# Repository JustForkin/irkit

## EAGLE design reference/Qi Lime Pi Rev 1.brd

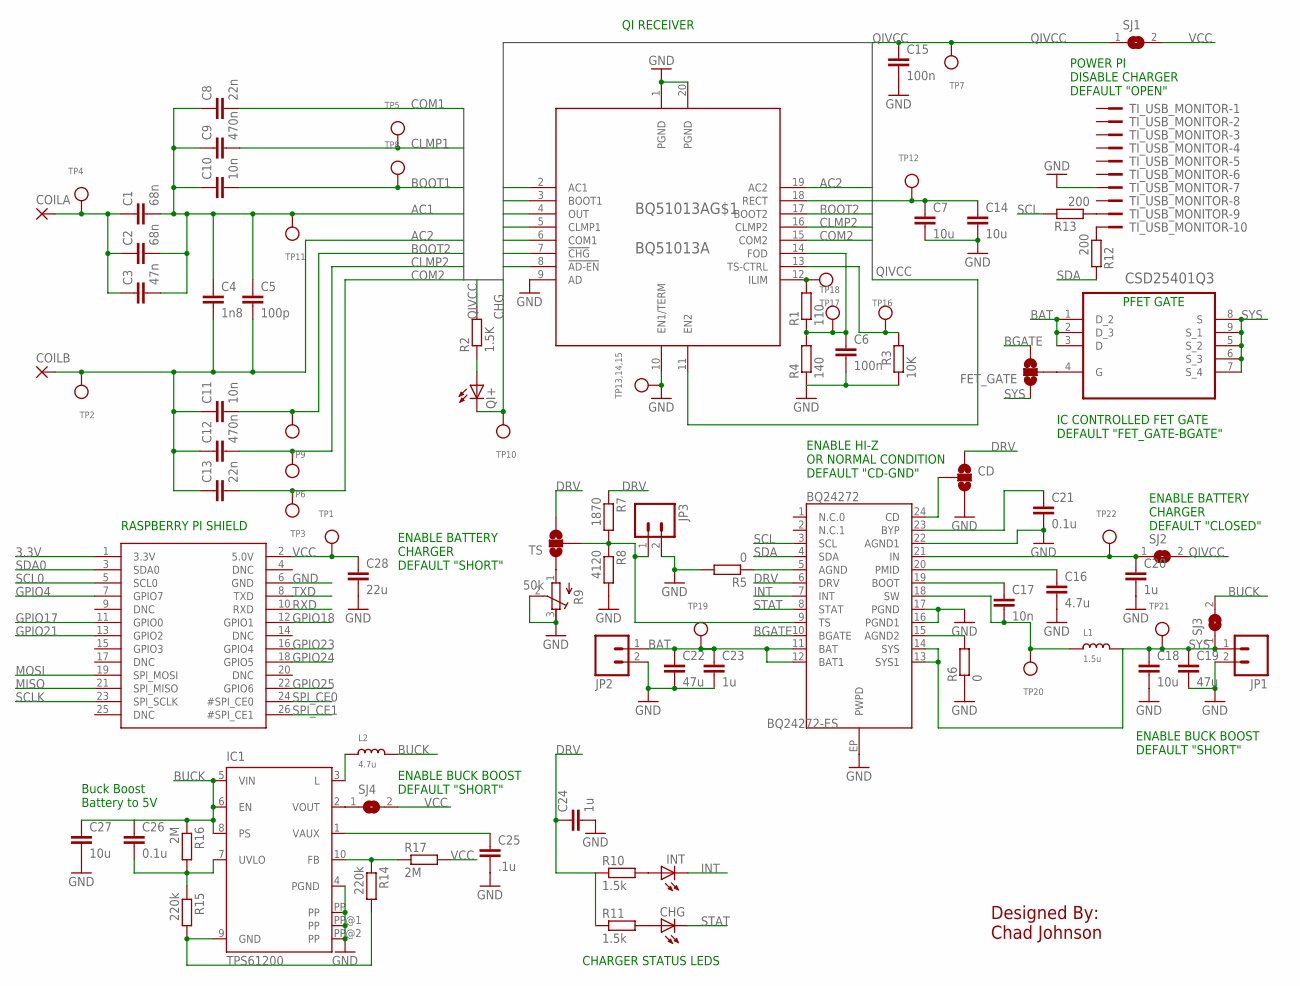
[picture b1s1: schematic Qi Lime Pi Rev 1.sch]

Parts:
BQ24272: BQ24272-ES; QFN-24_ALT2
BQ51013A: BQ51013A; RHL_R-VQFN-N20
C1, C2: 68n; C0603K; MPN C0603C682K5RACTU
C3: 47n; C0603K; MPN C0603C473K5RACTU
C4: 1n8; C0603K; MPN C0603C182K5RACTU
C5: 100p; C0603K; MPN C0603C101K5RACTU
C6, C15: 100n; C0603K
C7, C14, C18, C27: 10u; C0603K
C8, C13: 22n; C0603K; MPN C0603C223K5RACTU
C9, C12: 470n; C0603K
C10, C11, C17: 10n; C0603K
C16: 4.7u; C0603K
C19, C22: 47u; C0603K
C20, C23, C24: 1u; C0603K
C21, C26: 0.1u; C0603K
C25: .1u; C0603K
C28: 22u; C0603K
CD: SOLDERJUMPER_2WAYS; SJ_3
CHG: LEDCHIP-LED0603; CHIP-LED0603
COILA: 1,6/0,8
COILB: 1,6/0,8
CSD25401Q3: CSD25401Q3; SON65P300X300X-9N
FET_GATE: SOLDERJUMPER_2WAYS; SJ_3
IC1: TPS61200; S-PDSO-N10
INT: LEDCHIP-LED0603; CHIP-LED0603
JP1, JP2, JP3: M02PTH3; 1X02_LONGPADS
L1: 1.5u; INDUCTOR_5X5MM_NR5040_NOTHERMALS
L2: 4.7u; INDUCTOR_5X5MM_NR5040_NOTHERMALS
QI+: LEDCHIP-LED0603; CHIP-LED0603
R1: 110; R0402; MPN ERJ3EKF3000V
R2: 1.5K; R0402; MPN ERJ3EKF3000V
R3: 10K; R0402; MPN ERJ3EKF3000V
R4: 140; R0402; MPN ERJ3EKF3000V
R5, R6: 0; R0402; MPN ERJ3EKF3000V
R7: 1870; R0402; MPN ERJ3EKF3000V
R8: 4120; R0402; MPN ERJ3EKF3000V
R9: 50k; RTRIM64Y
R10, R11: 1.5k; R0402; MPN ERJ3EKF3000V
R12, R13: 200; R0402; MPN ERJ3EKF3000V
R14, R15: 220k; R0402; MPN ERJ3EKF3000V
R16, R17: 2M; R0402; MPN ERJ3EKF3000V
SJ1, SJ2, SJ3, SJ4: SJ
TI_USB_MONITOR: 2510-; PAK100/2500-10
TP1, TP2, TP3, TP4, TP5, TP6, TP7, TP8, TP9, TP10, TP11, TP12, TP13,14,15, TP16, TP17, TP18, TP19, TP20, TP21, TP22: TESTPOINTROUND1MM; TESTPOINT_ROUND_1MM
TS: SOLDERJUMPER_2WAYS; SJ_3
U$1: RASPBERRYPI_BB; RASBERRYPI_SHIELD

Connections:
3.3V: U$1.1 (3.3V)
AC1: BQ51013A.2 (AC1), C1.2, C2.2, C3.2, C4.1, C5.1, C8.1, C9.1, C10.1, TP11.P$1
AC2: BQ51013A.19 (AC2), C4.2, C5.2, C11.1, C12.1, C13.1, COILB.1, TP2.P$1
AD-EN: BQ51013A.8 (!AD-EN)
BAT: BQ24272.11 (BAT), BQ24272.12 (BAT1), C22.1, C23.1, CSD25401Q3.1 (D_2), CSD25401Q3.2 (D_3), CSD25401Q3.3 (D), JP2.1, TP19.P$1
BGATE: BQ24272.10 (BGATE), FET_GATE.3
BOOT1: BQ51013A.3 (BOOT1), C10.2, TP8.P$1
BOOT2: BQ51013A.17 (BOOT2), C11.2, TP9.P$1
BUCK: C26.1, C27.1, IC1.5 (VIN), IC1.6 (EN), IC1.8 (PS), L2.P$2 (2), R16.1, SJ3.2
CHG: BQ51013A.7 (!CHG), QI+.C, TP10.P$1
CLMP1: BQ51013A.5 (CLMP1), C9.2, TP5.P$1
CLMP2: BQ51013A.16 (CLMP2), C12.2, TP6.P$1
COM1: BQ51013A.6 (COM1), C8.2
COM2: BQ51013A.15 (COM2), C13.2, TP3.P$1
DRV: BQ24272.6 (DRV), C24.1, CD.1, R7.1, R10.1, R11.1, TS.3
FOD: BQ51013A.14 (FOD), C6.1, R1.1, R4.2, TP17.P$1
GND: BQ24272.16 (PGND1), BQ24272.17 (PGND), BQ24272.22 (AGND1), BQ24272.EP (PWPD), BQ51013A.1 (PGND), BQ51013A.9 (AD), BQ51013A.10 (EN1/TERM), BQ51013A.20 (PGND), C6.2, C7.2, C14.2, C15.2, C16.2, C18.2, C19.2, C20.2, C21.2, C22.2, C23.2, C24.2, C25.2, C27.2, C28.2, CD.3, IC1.4 (PGND), IC1.PP, IC1.PP@1 (PP), IC1.PP@2 (PP), JP1.2, JP2.2, JP3.2, R3.1, R4.1, R5.2, R6.1, R8.2, R9.2 (S), R9.3 (E), TI_USB_MONITOR.7, TP13,14,15.P$1, U$1.6 (GND)
GPIO4: U$1.7 (GPIO7)
GPIO17: U$1.11 (GPIO0)
GPIO18: U$1.12 (GPIO1)
GPIO21: U$1.13 (GPIO2)
GPIO23: U$1.16 (GPIO4)
GPIO24: U$1.18 (GPIO5)
GPIO25: U$1.22 (GPIO6)
INT: BQ24272.7 (INT), INT.C
MISO: U$1.21 (SPI_MISO)
MOSI: U$1.19 (SPI_MOSI)
unnamed: BQ51013A.12 (ILIM), R1.2, TP18.P$1
unnamed: BQ24272.5 (AGND), R5.1
unnamed: BQ24272.21 (IN), C20.1, SJ2.1, TP22.P$1
unnamed: R9.1 (A), TS.1
unnamed: BQ24272.20 (PMID), C16.1
unnamed: BQ24272.19 (BOOT), C17.1
unnamed: C1.1, C2.1, C3.1, COILA.1, TP4.P$1
unnamed: BQ24272.18 (SW), C17.2, L1.P$1 (1), TP20.P$1
unnamed: BQ24272.23 (BYP), C21.1
unnamed: BQ24272.15 (AGND2), R6.2
unnamed: BQ24272.24 (CD), CD.2
unnamed: BQ24272.9 (TS), JP3.1, R7.2, R8.1, TS.2
unnamed: INT.A, R10.2
unnamed: CHG.A, R11.2
unnamed: R13.1, TI_USB_MONITOR.9
unnamed: R12.1, TI_USB_MONITOR.10
unnamed: CSD25401Q3.4 (G), FET_GATE.2
unnamed: C25.1, IC1.1 (VAUX)
unnamed: BQ51013A.13 (TS-CTRL), R3.2, TP16.P$1
unnamed: QI+.A, R2.1
unnamed: IC1.3 (L), L2.P$1 (1)
unnamed: IC1.10 (FB), R14.1, R17.1
unnamed: C26.2, IC1.7 (UVLO), R15.1, R16.2
unnamed: IC1.2 (VOUT), SJ4.1
unnamed: IC1.9 (GND), R14.2, R15.2
QIVCC: BQ51013A.4 (OUT), BQ51013A.11 (EN2), C15.1, R2.2, SJ1.1, SJ2.2, TP7.P$1
RECT: BQ51013A.18 (RECT), C7.1, C14.1, TP12.P$1
RXD: U$1.10 (RXD)
SCL: BQ24272.3 (SCL), R13.2
SCL0: U$1.5 (SCL0)
SCLK: U$1.23 (SPI_SCLK)
SDA: BQ24272.4 (SDA), R12.2
SDA0: U$1.3 (SDA0)
SPI_CE0: U$1.24 (#SPI_CE0)
SPI_CE1: U$1.26 (#SPI_CE1)
STAT: BQ24272.8 (STAT), CHG.C
SYS: BQ24272.13 (SYS1), BQ24272.14 (SYS), C18.1, C19.1, CSD25401Q3.5 (S_2), CSD25401Q3.6 (S_3), CSD25401Q3.7 (S_4), CSD25401Q3.8 (S), CSD25401Q3.9 (S_1), FET_GATE.1, JP1.1, L1.P$2 (2), SJ3.1, TP21.P$1
TXD: U$1.8 (TXD)
VCC: C28.1, R17.2, SJ1.2, SJ4.2, TP1.P$1, U$1.2 (5.0V)

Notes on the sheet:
ENABLE BATTERY CHARGER DEFAULT "CLOSED"
ENABLE BUCK BOOST DEFAULT "SHORT"
POWER PI DISABLE CHARGER DEFAULT "OPEN"
RASPBERRY PI SHIELD
CHARGER STATUS LEDS
QI RECEIVER
ENABLE BATTERY CHARGER DEFAULT "SHORT"
IC CONTROLLED FET GATE DEFAULT "FET_GATE-BGATE"
ENABLE HI-Z OR NORMAL CONDITION DEFAULT "CD-GND"
PFET GATE
Buck Boost Battery to 5V
Designed By: Chad Johnson

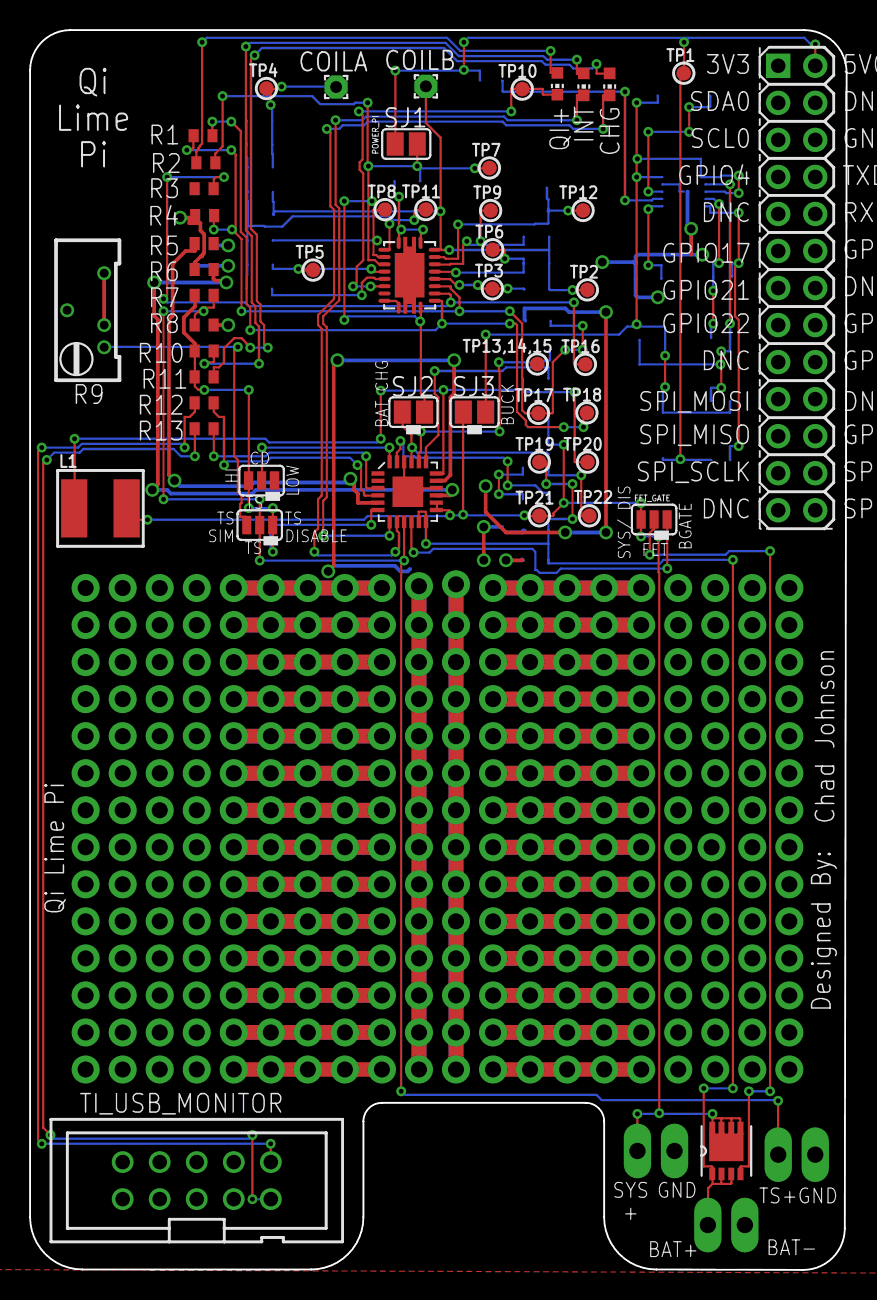
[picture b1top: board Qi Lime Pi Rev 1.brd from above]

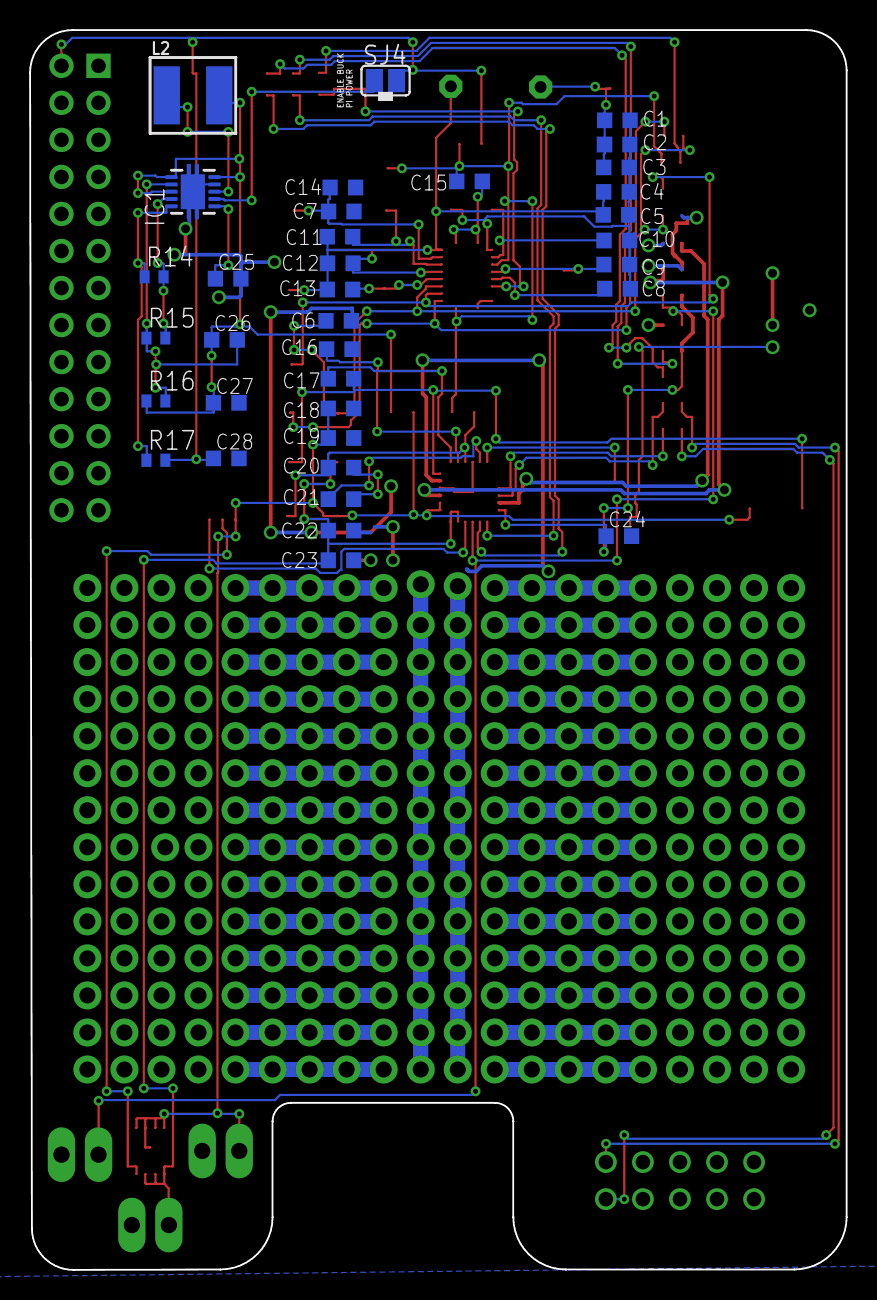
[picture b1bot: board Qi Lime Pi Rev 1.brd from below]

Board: 2 copper layers, 56.0 x 85.0 mm, 88 parts (35 on the bottom side), 48 nets.

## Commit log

2013-03-03 merging all files in one go
2013-03-05 cleaned up
2013-03-05 report
2013-03-05 rotated
2013-03-20 sending images to site; used os.system commands to fix errors on R-Pi
2013-04-27 reorganized
2013-04-27 cleaning
2013-04-27 started shield
2013-04-29 updated shield and peripheral
2013-04-29 added images
2013-04-29 added another image
2013-04-29 udpated photos
2013-04-29 added sketch
2013-04-29 added readme
2013-04-29 reademe

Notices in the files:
parts and their libraries:
microbuilder1: This work is placed in the public domain, and may be freely used for commercial and non-commercial work with the following conditions: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
chad1: Licensing: CC v3.0 Share-Alike You are welcome to use this library for commercial purposes.
